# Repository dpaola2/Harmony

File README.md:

# Offline MP3 Player (Harmony2)

Hardware-agnostic MP3 player core with a PC simulator and ESP32 targets. See `docs/README.md` for the doc map; hardware bring-up for Prototype 1 is in `hardware/prototype1/README.md`.

## Current Mark-6 build

The active player uses native ESP-IDF firmware on the Adafruit ESP32 Feather V2. The Python/MicroPython architecture below is retained historical context.

- [Feather bench firmware and instructions](firmware/mark-6/feather-player-bench/README.md)
- [Native UI and renderer](firmware/mark-6/feather-carrier/main/)
- [UI requirements and completion status](docs/Harmony-player-ui-requirements.md)
- [Desktop UI prototype](platforms/pc/ui/README.md)
- [Preserved Mark-7 visual reference](docs/mark-7-design-reference.md)
- [Changelog](CHANGELOG.md)

## Architecture & Goals
- Core app logic in Python, shared by PC simulator and MicroPython on ESP32.
- iPod-style UI: Library → Now Playing → Settings with tactile buttons (no touch).
- Portable storage (SD) and Bluetooth audio on hardware targets; PC sim for fast iteration.
- More context: `PROJECT_OVERVIEW.md` (goals/constraints) and `PLAN.md` (roadmap).

## Development
- **Environment (macOS)**:
  - Install Homebrew if missing: `/bin/bash -c "$(curl -fsSL https://raw.githubusercontent.com/Homebrew/install/HEAD/install.sh)"`.
  - Python: `brew install python` (or `pyenv` if you prefer pinned versions).
  - Recommended tooling: `pipx install uv` (or `pip install uv` in a venv); `pipx ensurepath`.
  - Create venv: `python -m venv .venv && source .venv/bin/activate`.
  - Install dev deps: `python -m pip install --upgrade pip uv pytest`.

- **Run PC simulator** (console UI):
  ```bash
  source .venv/bin/activate
  python -m platforms.pc.main_pc [--music-dir /path/to/Artist/Album/Track.ext]
  ```
  Controls: `w/s` up/down, `a` left, `d` right, `space`/Enter select, `p` play/pause, `b` or `q` back, `x` quit, `+`/`=` volume up, `-` volume down. Defaults to an in-memory demo library.

- **Tests**:
  ```bash
  source .venv/bin/activate
  pytest
  ```
  (Targets `core/` behavior.)

- **ESP32 Prototype 1 upload (demo UI, no buttons required)**:
  - See `hardware/prototype1/README.md` for wiring and flashing details.
  - Convenience script from repo root:
    ```bash
    scripts/upload_proto1_demo.sh /dev/tty.usbmodem*   # adjust port as needed
    ```
    It copies `core/`, `platforms/esp32/*.py`, and `main_esp32.py` to the board and keeps `main.py` as entrypoint.

## Repo structure
- `core/` hardware-agnostic logic and models
- `platforms/pc/` PC simulator (console screen, keyboard input, audio backend)
- `platforms/esp32/` ESP32 adapters (screen, buttons, audio)
- `hardware/` wiring/board notes (prototype phases)
- `enclosure/` mechanical notes
- `tests/` pytest cases for `core/`

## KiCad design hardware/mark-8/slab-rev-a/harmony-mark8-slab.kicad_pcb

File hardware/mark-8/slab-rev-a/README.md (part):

# Harmony Mark-8 "slab" board, revision A

This is the main board of the Mark-8 slab music player, built from `SPEC.md`. It is a 4-layer, 0.8 mm board of 54.4 x 39.6 mm. Every part is on one side and JLCPCB places all of them. When the boards arrive, Dave only flashes them, then adds the screen, the battery and the printed case. No soldering is needed, except for the optional vibration motor (two joints).

**Status: ready to order, with accepted exceptions.** The fixes of the 2026-11-21 pre-order review and of the change review that checked them are in (see "Review dispositions, November 21", its "Change review" table and "Decisions"). ERC 0 errors, 0 warnings; DRC 0 errors, 0 unconnected, 32 silkscreen warnings; `verify.py` passes. The board comes from step C of the touch-wheel re-route: it keeps the checked routing from before the touch review, with the review's layout fixes applied on top by `review_fixes.py`. Eight slow switching nets keep their L3 track behind the touch electrodes, and the two main VBUS paths keep a 0.2 mm bottleneck. Both are accepted exceptions with caps in `design.py`, and the firmware must follow "Firmware for the touch wheel" (see "Touch-wheel re-route"). JLC receives the board in its own frame with rails (`jlcpcb/ORDER.md`). Nothing has been uploaded or ordered.

## What is on the board

```
USB-C J1 ──ESD U8──┬─ D+/D- ── CH9102F U2 ── TXD/RXD (1k) ── ESP32 U1 (UART0)
                   │                   └─ DTR/RTS ── UMH3N Q1 ── EN / IO0
                   ├─ VBUS ── B5819W D1 ───────────────┐
                   ├─ VBUS ── MCP73831 U3 ── VBAT ──────┤
                   └─ CC1/CC2 5.1k to GND              │
JST PH J4 ── AO3401A Q2 (reverse battery) ── VBAT ── AO3401A Q3 (off while VBUS) ── VSYS
                                               │                                    │
                                     MAX17048 U5 (I2C 0x36)      RT9080 U4 ── 3V3 ──┼── ESP32 U1, MPR121 U6, MAX17048 U5 logic
                                                                                    │      └─ AO3401A Q4 ── 3V3_PERIPH ── screen J2, microSD J3
                                                    VSYS ── 10R ── screen LEDA; LEDK ── AO3400A Q5 ── GND (IO4 PWM)
                                                    VSYS ── 33R ── buzzer BZ1 ── AO3400A Q6 (IO2)
                                                    VSYS ── DRV2605L U7 (I2C 0x5A) ── motor pads M+ M-
ESP32 HSPI (14/27/26/33/32, TE 39) ── FH35C J2 (screen)      ESP32 VSPI (5/19/21/25, CD 15) ── DM3AT J3 (microSD)
ESP32 I2C (22/20) ── U5 0x36, U6 0x5B, U7 0x5A               MPR121 U6 ── 9 electrodes on L4 (E1)
```

| Ref | Part | LCSC |
| --- | --- | --- |
| U1 | ESP32-PICO-MINI-02-N8R2 | C2980306 |
| U2 | CH9102F USB to serial | C2858418 |
| U3 | MCP73831T-2ACI/OT charger, PROG 2.7k (about 370 mA) | C424093 |
| U4 | RT9080-33GJ5 3.3 V regulator | C841192 |
| U5 | MAX17048G+T10 fuel gauge | C2682616 |
| U6 | MPR121QR2 touch controller | C91322 |
| U7 | DRV2605LDGSR haptic driver | C527464 |
| U8 | USBLC6-2SC6 USB ESD | C7519 |
| J1 | HRO TYPE-C-31-M-12 USB-C | C165948 |
| J2 | Hirose FH35C-15S-0.3SHW(50) screen FPC | C2889267 |
| J3 | Hirose DM3AT-SF-PEJM5 microSD | C114218 |
| J4 | XYECONN XY-S2B-PH-SM4-TB (JST PH 2.0 side entry) | C54582899 |
| SW1 | Alps SKRTLAE010 side button | C110293 |
| SW2, SW3 | TS-1088-AR02016 BOOT, RESET | C720477 |
| BZ1 | MLT-5020 magnetic buzzer | C94598 |
| Q1 | UMH3N auto-reset | C62892 |
| Q2, Q3, Q4 | AO3401A | C15127 |
| Q5, Q6 | AO3400A | C20917 |
| D1, D2 | B5819W SL | C8598 |
| LED1 | KT-0603R red | C2286 |

The full BOM (40 lines) is `jlcpcb/bom.csv`; the netlist is `netlist.xml`; the schematic is `harmony-mark8-slab.kicad_sch` and `review/schematic.pdf`.

## ESP32 pin map

| GPIO | Module pin | Net | Connects to |
| --- | --- | --- | --- |
| EN | 8 | ESP_EN | 10k to 3V3 (R5), 1 uF (C4), RESET SW3, Q1 |
| 0 | 23 | BOOT | 10k to 3V3 (R6), BOOT SW2, Q1 |
| 1 TXD0 | 31 | U0TXD | 1k R3 to U2 RXD; test pad TP5 |
| 3 RXD0 | 30 | U0RXD | 1k R4 from U2 TXD; test pad TP6 |
| 14 | 18 | LCD_SCK | J2 pin 5 SCLK |
| 27 | 17 | LCD_MOSI | J2 pin 4 SDA |
| 26 | 16 | LCD_CS | J2 pin 7 |
| 33 | 13 | LCD_DC | J2 pin 6 RS |
| 32 | 12 | LCD_RST | J2 pin 8 |
| 4 | 24 | LCD_BL | 100R R15 to Q5 gate, 100k R16 pull-down |
| 39 | 7 | LCD_TE | J2 pin 3 FMARK |
| 5 | 29 | SD_SCK | J3 pin 5 CLK |
| 19 | 33 | SD_MOSI | J3 pin 3 CMD |
| 21 | 35 | SD_MISO | J3 pin 7 DAT0, 10k R21 to 3V3_PERIPH |
| 25 | 15 | SD_CS | J3 pin 2 DAT3, 10k R22 to 3V3_PERIPH |
| 15 | 21 | SD_CD | J3 card-detect switch to GND, 1M R25 to 3V3 |
| 22 | 34 | I2C_SDA | 4.7k R31; U5, U6, U7; test pad TP9 |
| 20 | 26 | I2C_SCL | 4.7k R32; U5, U6, U7; test pad TP10 |
| 34 | 9 | TOUCH_IRQ | U6 IRQ, 10k R11 |
| 38 | 6 | SIDE_BTN | SW1 to GND, 100k R26, 100 nF C23 |
| 13 | 20 | PERIPH_EN_N | 1k R14 to PERIPH_DIV (2.2k R13 to 3V3), 4.7k R34 on to the Q4 gate (1 uF C18 gate to source, 100 nF C26 gate to drain) |
| 2 | 22 | BUZZER | 100R R19 to Q6 gate, 100k R20 pull-down |
| 35 | 10 | VBAT_SENSE | VBAT through 1M R27 / 1M R28, 100 nF C24 |
| 36 | 4 | VBUS_SENSE | VBUS through 100k R29 / 75k R30 (VBUS = pin x 175 / 75) |
| 7, 8 | 27, 28 | GPIO7, GPIO8 | test pads TP7, TP8 |
| 12, 37 | 19, 5 | not connected | IO12 is the MTDI strap |

SD DAT1 and DAT2 have 10k pull-ups (R23, R24) to 3V3_PERIPH. J4: pin 2 is battery +, pin 1 is battery -, marked + and - on the silkscreen.

## Power

- USB VBUS feeds the charger U3, the CH9102F U2 (VDD5 and its VBUS sense) and, through D1, VSYS. C1 10 uF at J1, C7 4.7 uF at U3, C25 100 nF at U2.
- The battery connects through Q2 (P-MOSFET, drain on the J4 + pin, source on VBAT, gate on GND) to VBAT, which has C8 10 uF. Q3 (drain VBAT, source VSYS, gate on VBUS with R9 10k to GND) connects VBAT to VSYS while VBUS is absent. R9 is 10k (it was 100k) so that VBUS bleeds down in tens of milliseconds after an unplug: until it does, VSYS runs on Q3's body diode and 3V3 can sag (review PWR-5). It costs 0.5 mA while USB is plugged in.
- Q2 blocks a reversed pack only while USB is unplugged. With USB plugged in, the charger's preconditioning current turns Q2 on and slowly discharges a reversed pack (about 37 mA) while the charge LED shows charging (review PWR-2). Check the pack polarity with a meter before you connect it.
- VSYS (C9 22 uF) feeds U4 (RT9080, EN on VSYS, C10 1 uF in, C11 4.7 uF out), the 10 R backlight resistor R17, the 33 R buzzer resistor R18 and U7. C11 is a 4.7 uF 10 V X5R 0402 (about 2 uF at 3.3 V; the RT9080 needs more than 1 uF effective at the pin, review PWR-7). The 22 uF C5 at U1 sits behind about 0.22 ohm of track.
- 3V3 feeds U1 (C5 22 uF + C6 100 nF at pin 3), U5 logic side through the I2C pull-ups, U6, the I2C and button pull-ups, U2 VIO and Q4.
- Q4 switches 3V3 to 3V3_PERIPH (screen VCC and IOVCC, microSD VDD, the SD pull-ups). GPIO13 low turns it on, GPIO13 high turns it off. The gate network (review PWR-1, ESP32-2, FW-HW-1; `q4_gate_sim.py`, results in `review/q4-gate-sim.json`):
  - R13 2.2k (3V3 to PERIPH_DIV) and R14 1k (GPIO13 to PERIPH_DIV) form a divider. Driven low, it puts about 1 V on the gate (VGS -2.2 V, Q4 fully on; it draws 1 mA from 3V3 while the rail is on). While EN is low GPIO13 floats and R13 holds the gate at 3V3. After reset release GPIO13 has only its internal pull-down (45k typical, no limits given; simulated 30k to 80k), and the divider holds VGS at -0.09 to -0.22 V, below the AO3401A's -0.5 V minimum threshold: Q4 stays off from reset release until firmware drives GPIO13 low, also in download mode. Leakage at -0.22 V is about 0.2 uA (2.4 uA for a hot part at the threshold minimum).
  - Off means that Q4 does not conduct. It does not mean that 3V3_PERIPH is at 0 V. Until firmware runs, and all the time in download mode, the ESP32's reset pull-ups on GPIO5 (SD_SCK) and GPIO14 (LCD_SCK) feed the unpowered card and screen through their input clamps, so 3V3_PERIPH can sit at about 1 to 2.5 V (change review, Q4 missed item). The current is tens of microamps and harms nothing. To check Q4 at bring-up, hold the board in download mode and measure 3V3 minus PERIPH_GATE: it must be 0.25 V or less. 3V3_PERIPH under 0.1 V is a valid check only with the screen and the card removed.
  - R34 4.7k (PERIPH_DIV to PERIPH_GATE) and C26 100 nF (gate to drain) set the turn-on ramp: on the Miller plateau the gate current through R34 flows through C26, so the drain rises at a controlled rate. C18 1 uF (gate to source) keeps the gate on 3V3 while 3V3 itself powers up: VGS stays above about -0.37 V (with C18 15 percent low and C26 10 percent high), and the rail stays below 0.04 V.
  - Simulated across VGS(th) -0.5 to -1.3 V, K 5 to 18 A/V2, 10 to 30 uF and 0 to 100 mA on 3V3_PERIPH, the RT9080 at its 610 mA minimum current limit, C11 at 1.3 uF (the low end for the 4.7 uF 0402 at 3.3 V) and 250 mA for the ESP32: 3V3_PERIPH reaches 90 percent 3.3 to 10.1 ms after GPIO13 goes low (10 to 90 percent in 1.0 to 3.2 ms), Q4 peaks at 161 mA (100 mA of it the resistive load), and 3V3 at U1 stays at 3.22 V or more. The 3.22 V figure assumes the RT9080's nominal 3.30 V and a full battery. With the set point 2 percent low it is about 3.16 V, and with a low battery (VSYS 3.45 V, the RT9080 in dropout) about 3.03 to 3.09 V. The turn-on itself costs 10 mV or less (55 mV or less in dropout). The old network (100k, 10k, 100 nF) gave 0.36 to 1.0 ms, up to 0.96 A and 3V3 down to 1.74 V in the same model. Q4 stops conducting 3.5 to 10.6 ms after GPIO13 goes high at 25 C (up to about 21 ms for a hot part); the rail then drains slowly through its loads. After a reset, Q4 turns off up to about 20 ms after reset release (change review Q4-4).
  - C19 10 uF + C20 100 nF at J2, C21 10 uF + C22 100 nF at J3.
- U2 CH9102F: VDD5 and VBUS from USB VBUS, V3 decoupled by C2, VIO on 3V3 with C3. This is WCH's dual-supply scheme: on battery VDD5 is at 0 V, VIO draws about 2 uA and the chip does not back-feed (CH9102 datasheet 5.2).
- Deep-sleep estimate with Q4 off, U2 unpowered, U6 in stop mode, U7 in standby: ESP32-PICO-MINI-02 about 10 uA, U5 3 to 23 uA (hibernate or active), U6 about 3 uA, U7 about 4 uA, U4 2 uA, VBAT divider 2.1 uA, U3 reverse current under 2 uA, D1 reverse leakage 6 to 15 uA (review PWR-11): about 36 to 65 uA. With touch wake on (the player default), U6 runs a slow scan instead of stop mode: about 11 uA instead of 3. With a card in J3, the card-detect switch also draws 3.3 uA through R25 (3.3 V / 1M; it was 33 uA with 100k). All are under the 100 uA target.

Firmware notes that follow from the hardware:
1. Drive every screen and card line low, or make it an input, before setting GPIO13 high (Q4 off), or the ESP32 back-powers the screen and card through their input protection (SPEC 5.3).
2. Touch wake needs the MPR121 running (a slow scan), not stop mode. The 100 uA budget above assumes stop mode; measure the run-mode current before relying on touch wake.
3. The backlight runs from VSYS through 10 R: about 120 mA at 4.2 V battery and about 170 mA on USB (VSYS 4.7 V) at 100 percent duty, up to about 220 mA with a low-VF panel on a 5.25 V port (review PERIPH-2). R17 is a 1206 rated 0.25 W; keep the duty cycle at or below 80 percent on USB, and compute the R17 power cap from a worst-case model (VF 2.7 V, 10 ohm), not the brightness model.
4. GPIO15 (SD_CD) is the MTDO strap: a card in the slot silences the ROM boot log. GPIO2 (BUZZER) has R20 100k to GND, so the strap stays low at boot. R25 is 1M, so read SD_CD twice a few milliseconds apart before acting on a change.
5. The microSD lines are long and cross the touch wheel on L1 behind the L2 hatch (they do not go around it): SD_MOSI 88 mm, SD_SCK 82 mm (35 mm of it over the hatch), SD_MISO 77 mm, SD_CS 33 mm; the screen lines are 17 to 45 mm. SD_SCK has no series resistor: set the card's GPIOs to drive strength 0 or 1 before mounting (review L6). Start the card at 20 MHz SPI and drop to 10 MHz if reads fail.
6. Wait at least 20 ms after driving GPIO13 low before driving any screen or card line high (`SLAB_PERIPH_RAMP_MS`, see "Power"). After driving GPIO13 high, the rail needs about 0.4 s to drain below 0.5 V through its loads, so a real card power cycle needs that wait (review CC-2).
7. VBUS_SENSE is VBUS x 75 / 175: 5.0 V gives 2.14 V and 5.25 V gives 2.25 V at GPIO36, inside the ADC's calibrated range up to 5.7 V. `SLAB_VBUS_DIVIDER_X1000` is 2333; the 4300 mV present threshold is 1.84 V at the pin. GPIO36 has no filter capacitor (Espressif asks for 0.1 uF; the source is 43 kOhm), so average several ADC samples for each VBUS reading (change review Q4-5). Revision B adds 100 nF from GPIO36 to GND.

## Layout

The board sits behind the wheel, touch side (L4) against the front skin, component side toward the back plate. KiCad shows the component side, so left and right are swapped against the device front view. Every position in this README and in `mechanical-interface.json` is in device coordinates (SPEC 1); `design.py` holds the transform (`to_kicad`, `to_device`).

| Area (device) | What is there |
| --- | --- |
| Top left | J4 battery connector (cable to +Y), Q2, charger U3, Q3, D1, regulator U4, fuel gauge U5, bulk caps |
| Left edge, lower | haptic driver U7 and motor pads M+ M- |
| Behind the left part of the wheel (FPC leg zone) | Q4 and its gate network (R13, R14, R34, C18, C26) |
| Right edge | U1 with its antenna end flush with x = +27.2; SW1 side button above it, actuator through the right wall |
| Top right | BOOT SW2, RESET SW3, side-button RC, I2C pull-up R31 in the top strip; R32 just below the top buses, behind the wheel. Nothing in the antenna's open-end clearance below SW1 |
| Behind the wheel centre | MPR121 U6 with its parts, buzzer BZ1 and its driver, the J2 decoupling |
| Right of centre, just above the ramp zone | backlight switch Q5 (its body ends 0.05 above the ramp zone); its gate resistors R15 and R16 sit in the ramp zone (0402, 0.35 tall, under the 0.6 limit) |
| Bottom centre | USB-C J1 (mating face y = -50.4), screen connector J2 just above it (slot toward +X, into the empty ramp) |
| Bottom left | microSD J3 (card enters from -Y), its pull-ups in one row above the contacts, charge LED1 between J3 and J1 |
| Bottom right | ESD U8, CH9102F U2, auto-reset Q1, CC resistors, VBUS and VBAT sense dividers, EN RC |

### Touch wheel

- L4 carries nine copper zones: a centre disc r <= 7.0 and eight ring sectors from r 7.8 to 16.6, each boundary a three-tooth sawtooth (0.9 mm tangential half-amplitude) offset 0.2 each side, so neighbours are exactly 0.4 apart (checked by `verify.py`). ELE1 is at 12 o'clock seen from the front, then clockwise (`wheel.py`). Each electrode connects through one plated pad of E1 to an MPR121 pin, by an L1 track where one fits and otherwise partly on L3.
- L2 under the wheel is a 25 percent GND hatch (0.2 mm lines, 1.3 mm gaps, 45 degrees) out to r 17.6. The L4 GND pour and the L1 GND pour stop at r 17.6.
- L3 lies about 0.1 mm behind the L4 electrodes, with no ground between them. A track there couples into the electrode above it (about 0.5 pF per 10 mm of 0.15 mm track), and one edge during an MPR121 charge window can shift a reading by about as much as a touch (NXP AN3863: keep other signals on the far side of the ground layer). So inside the electrode disc plus 0.5 mm (r <= 17.1, `WHEEL_KEEPOUT_R`) only DC and static nets and the electrode lines may run on L3 or place vias: 3V3, 3V3_PERIPH, VBUS, VSYS, VBAT, BAT_P, LCD_RST, PERIPH_EN_N, PERIPH_DIV, PERIPH_GATE, SD_CD, SIDE_BTN, TOUCH_IRQ, BOOT, ESP_EN, CHG_STAT, VBAT_SENSE, VBUS_SENSE, GND and ELE0 to ELE8 (`WHEEL_TOLERANT_NETS` in `design.py`). BOOT, ESP_EN, PERIPH_DIV, PERIPH_GATE, CHG_STAT and the two sense dividers are not on the list the touch review gave; they only change at reset, at power switching or on a charge state change, never during a scan. LCD_LEDA is not static: with no capacitor on it, it swings 1.2 to 2.2 V at the backlight PWM rate (review PERIPH-1). Since 2026-11-21 it is an accepted exception like the seven below, not a DC net. VBUS (charger and adapter ripple while plugged in) and 3V3_PERIPH (card current spikes) also carry some AC, so log the touch noise while charging from a cheap adapter and during card read bursts too (review L10).
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
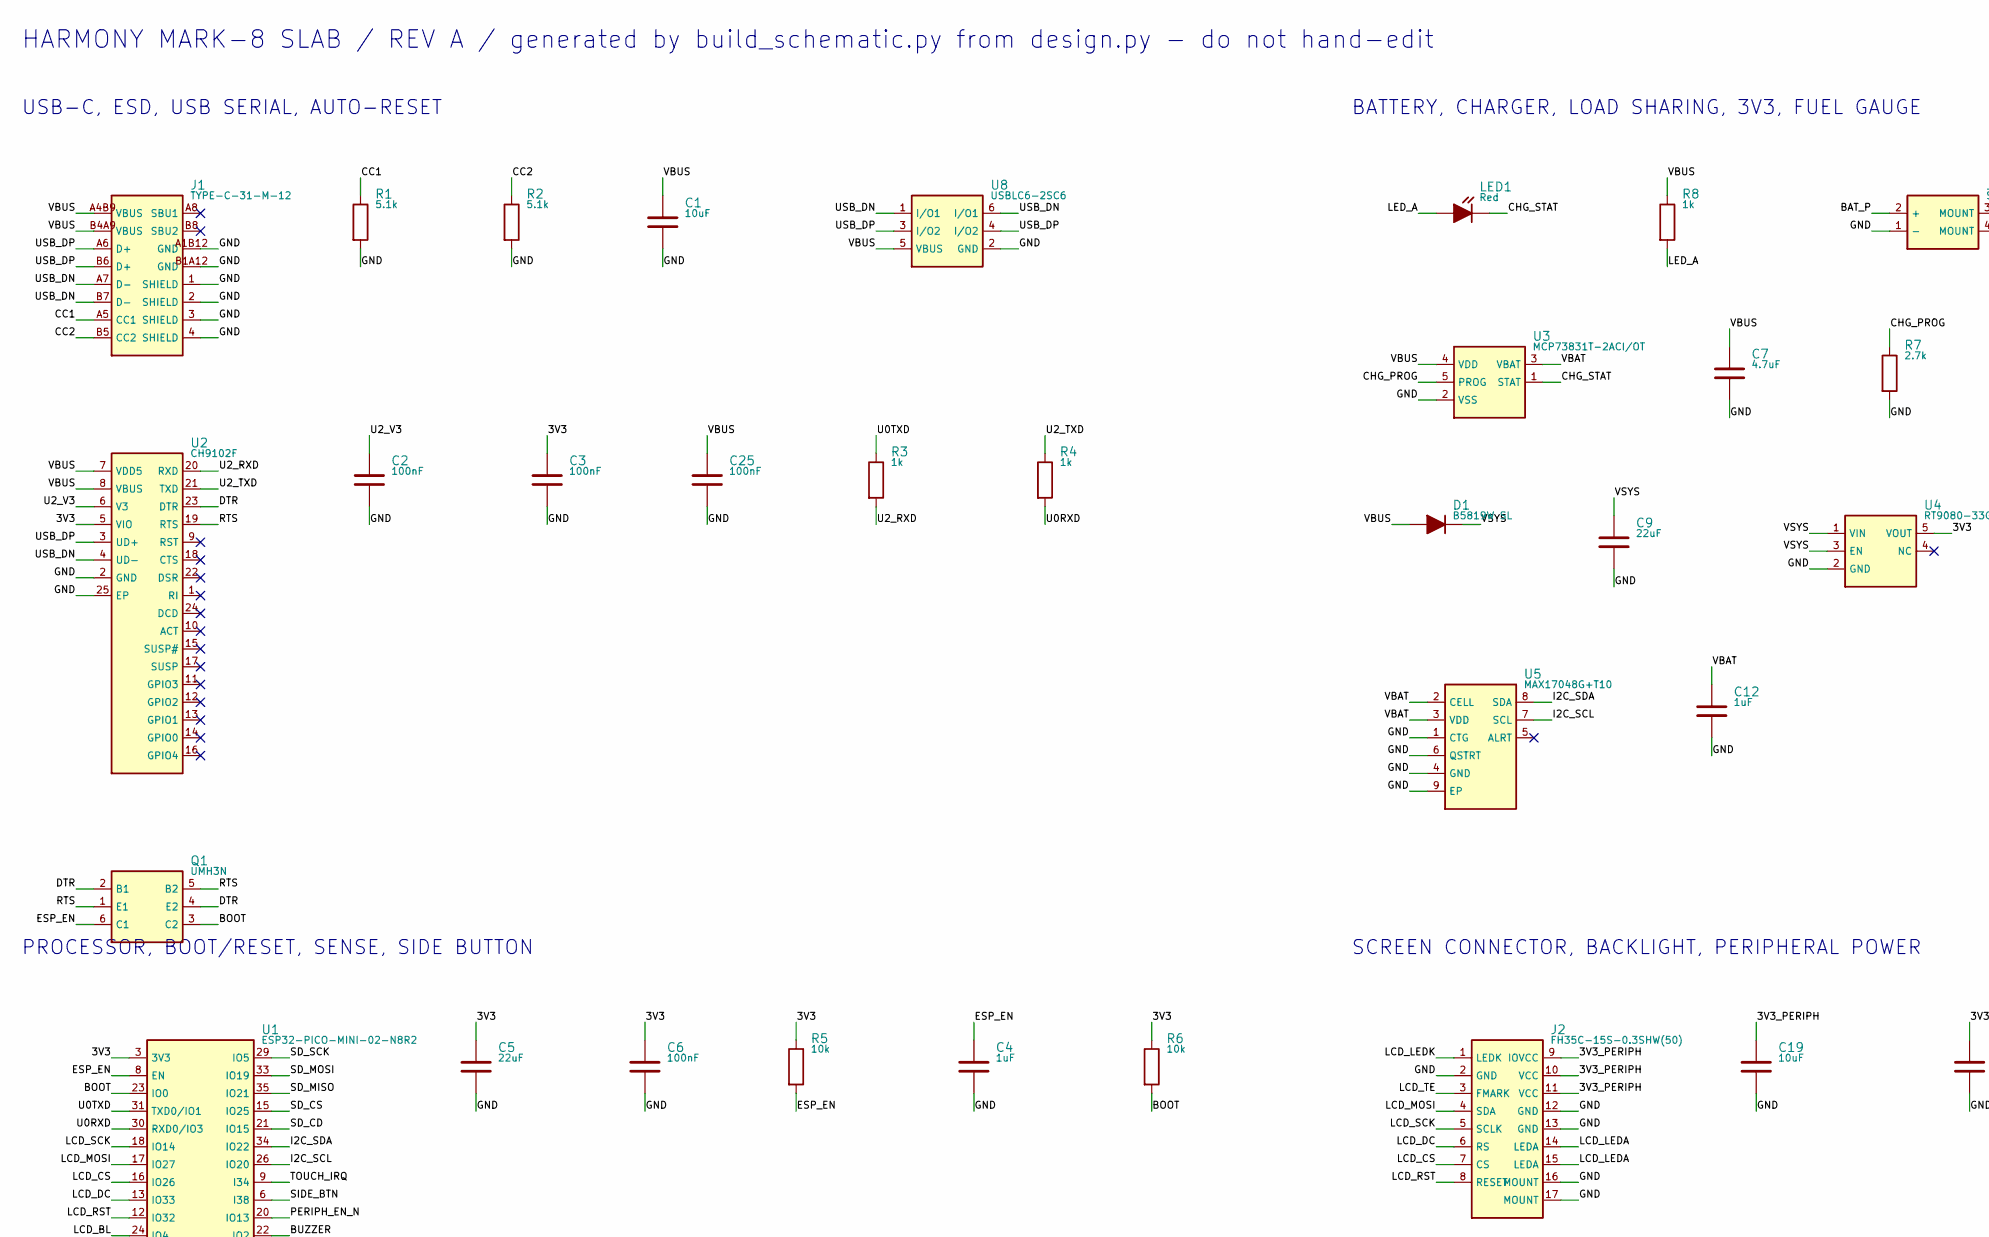
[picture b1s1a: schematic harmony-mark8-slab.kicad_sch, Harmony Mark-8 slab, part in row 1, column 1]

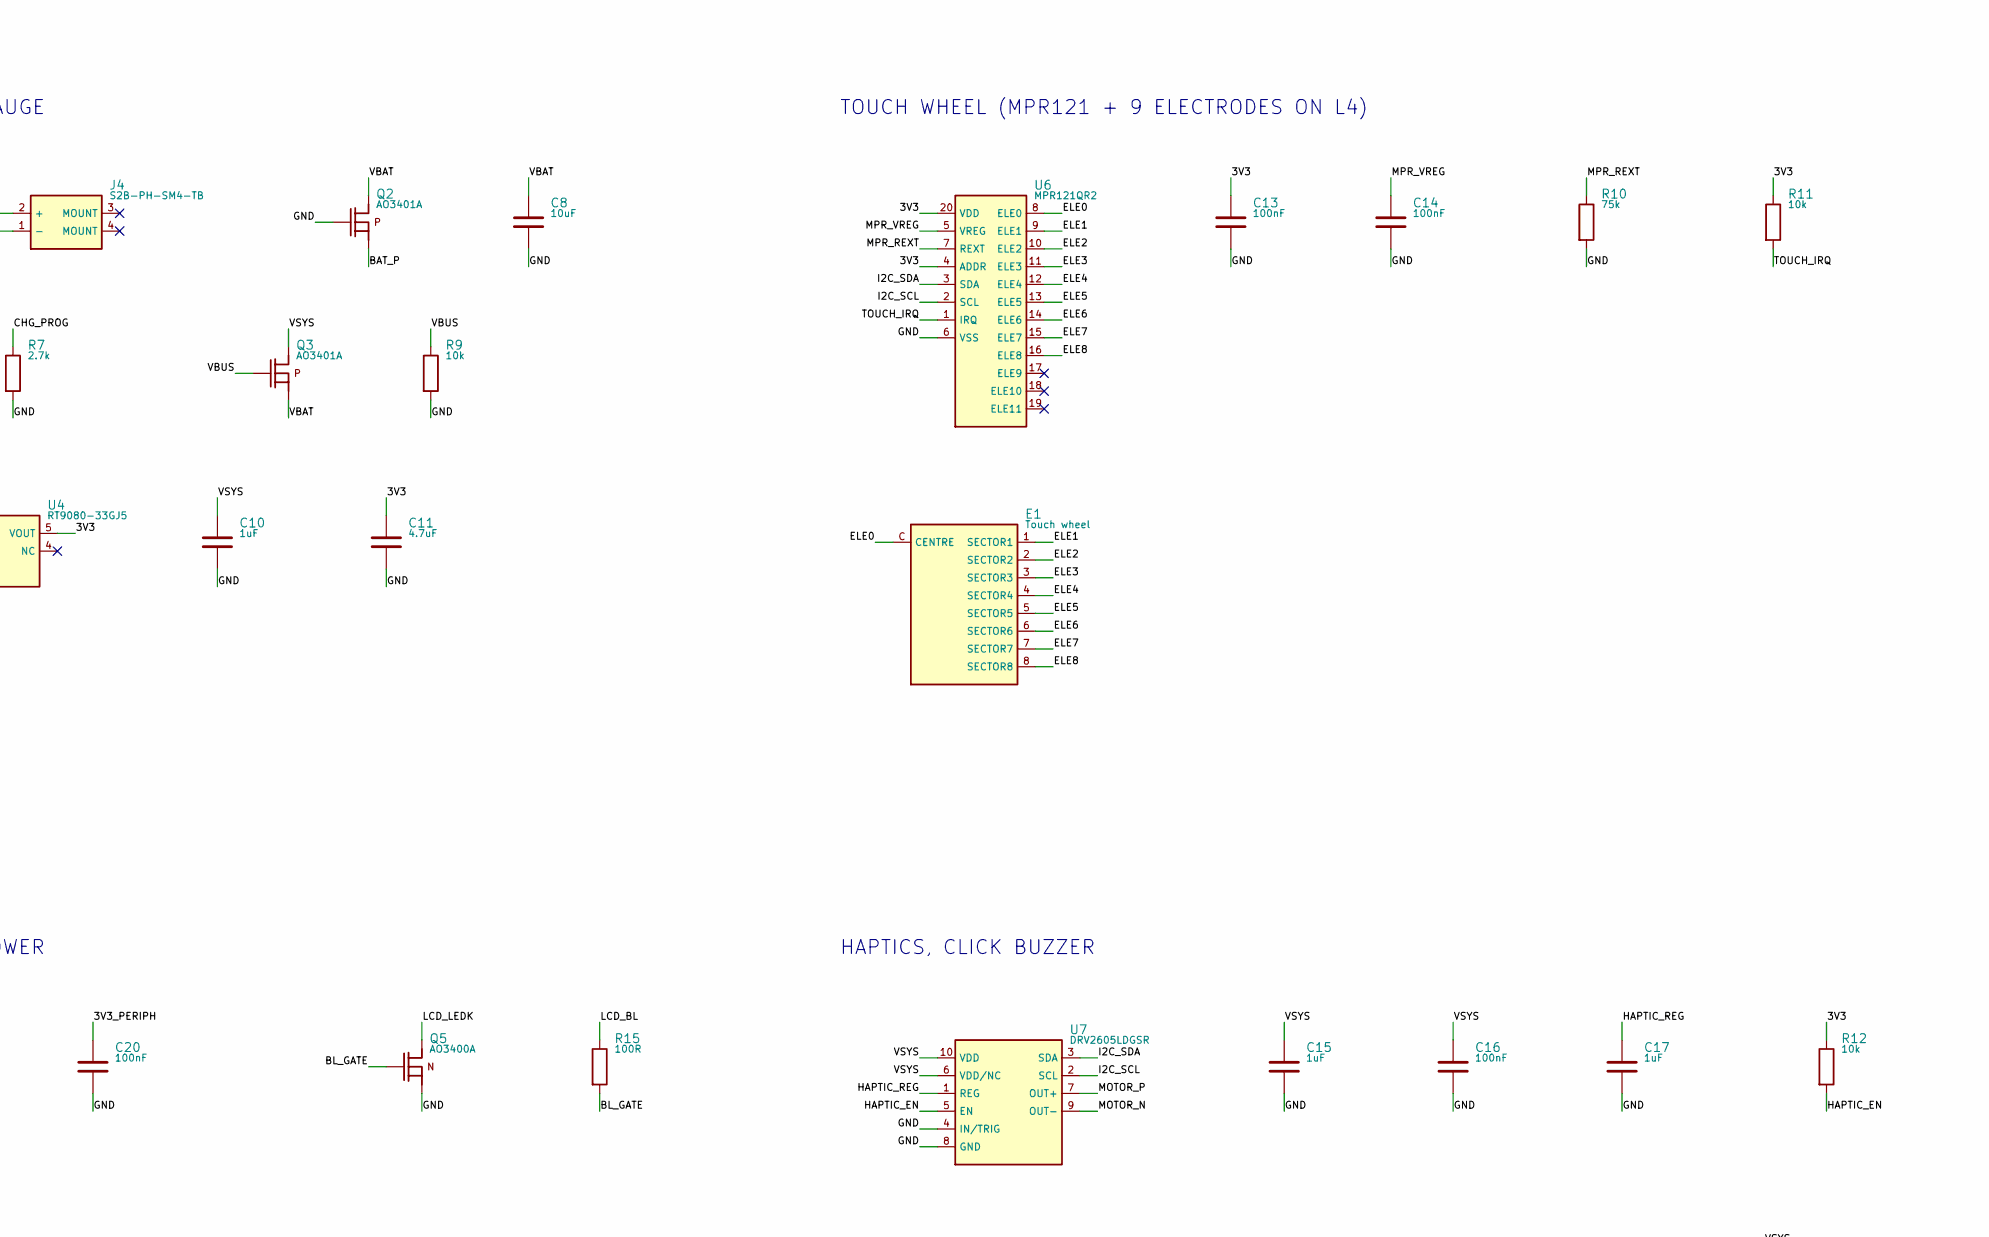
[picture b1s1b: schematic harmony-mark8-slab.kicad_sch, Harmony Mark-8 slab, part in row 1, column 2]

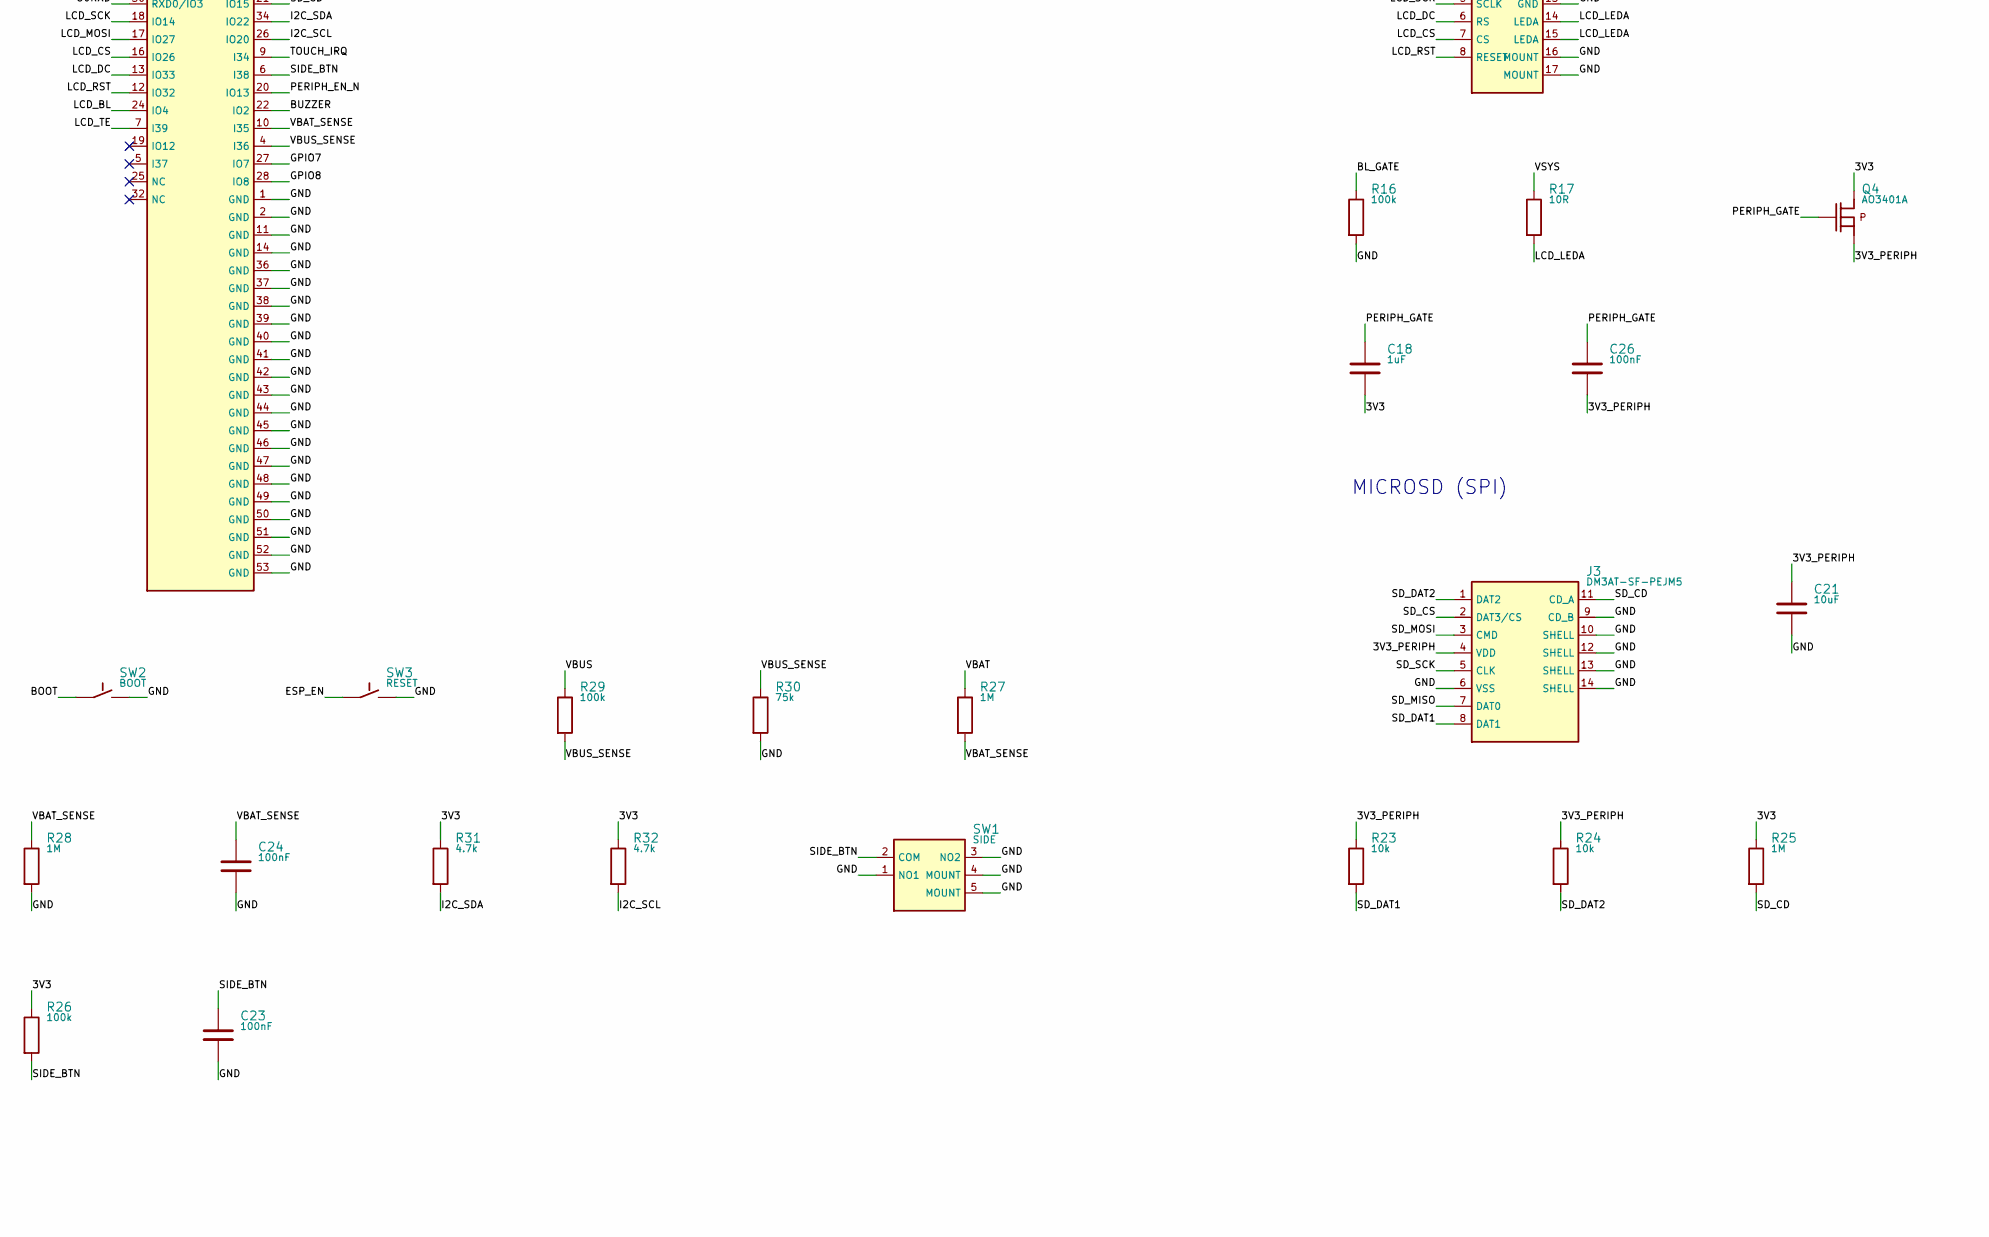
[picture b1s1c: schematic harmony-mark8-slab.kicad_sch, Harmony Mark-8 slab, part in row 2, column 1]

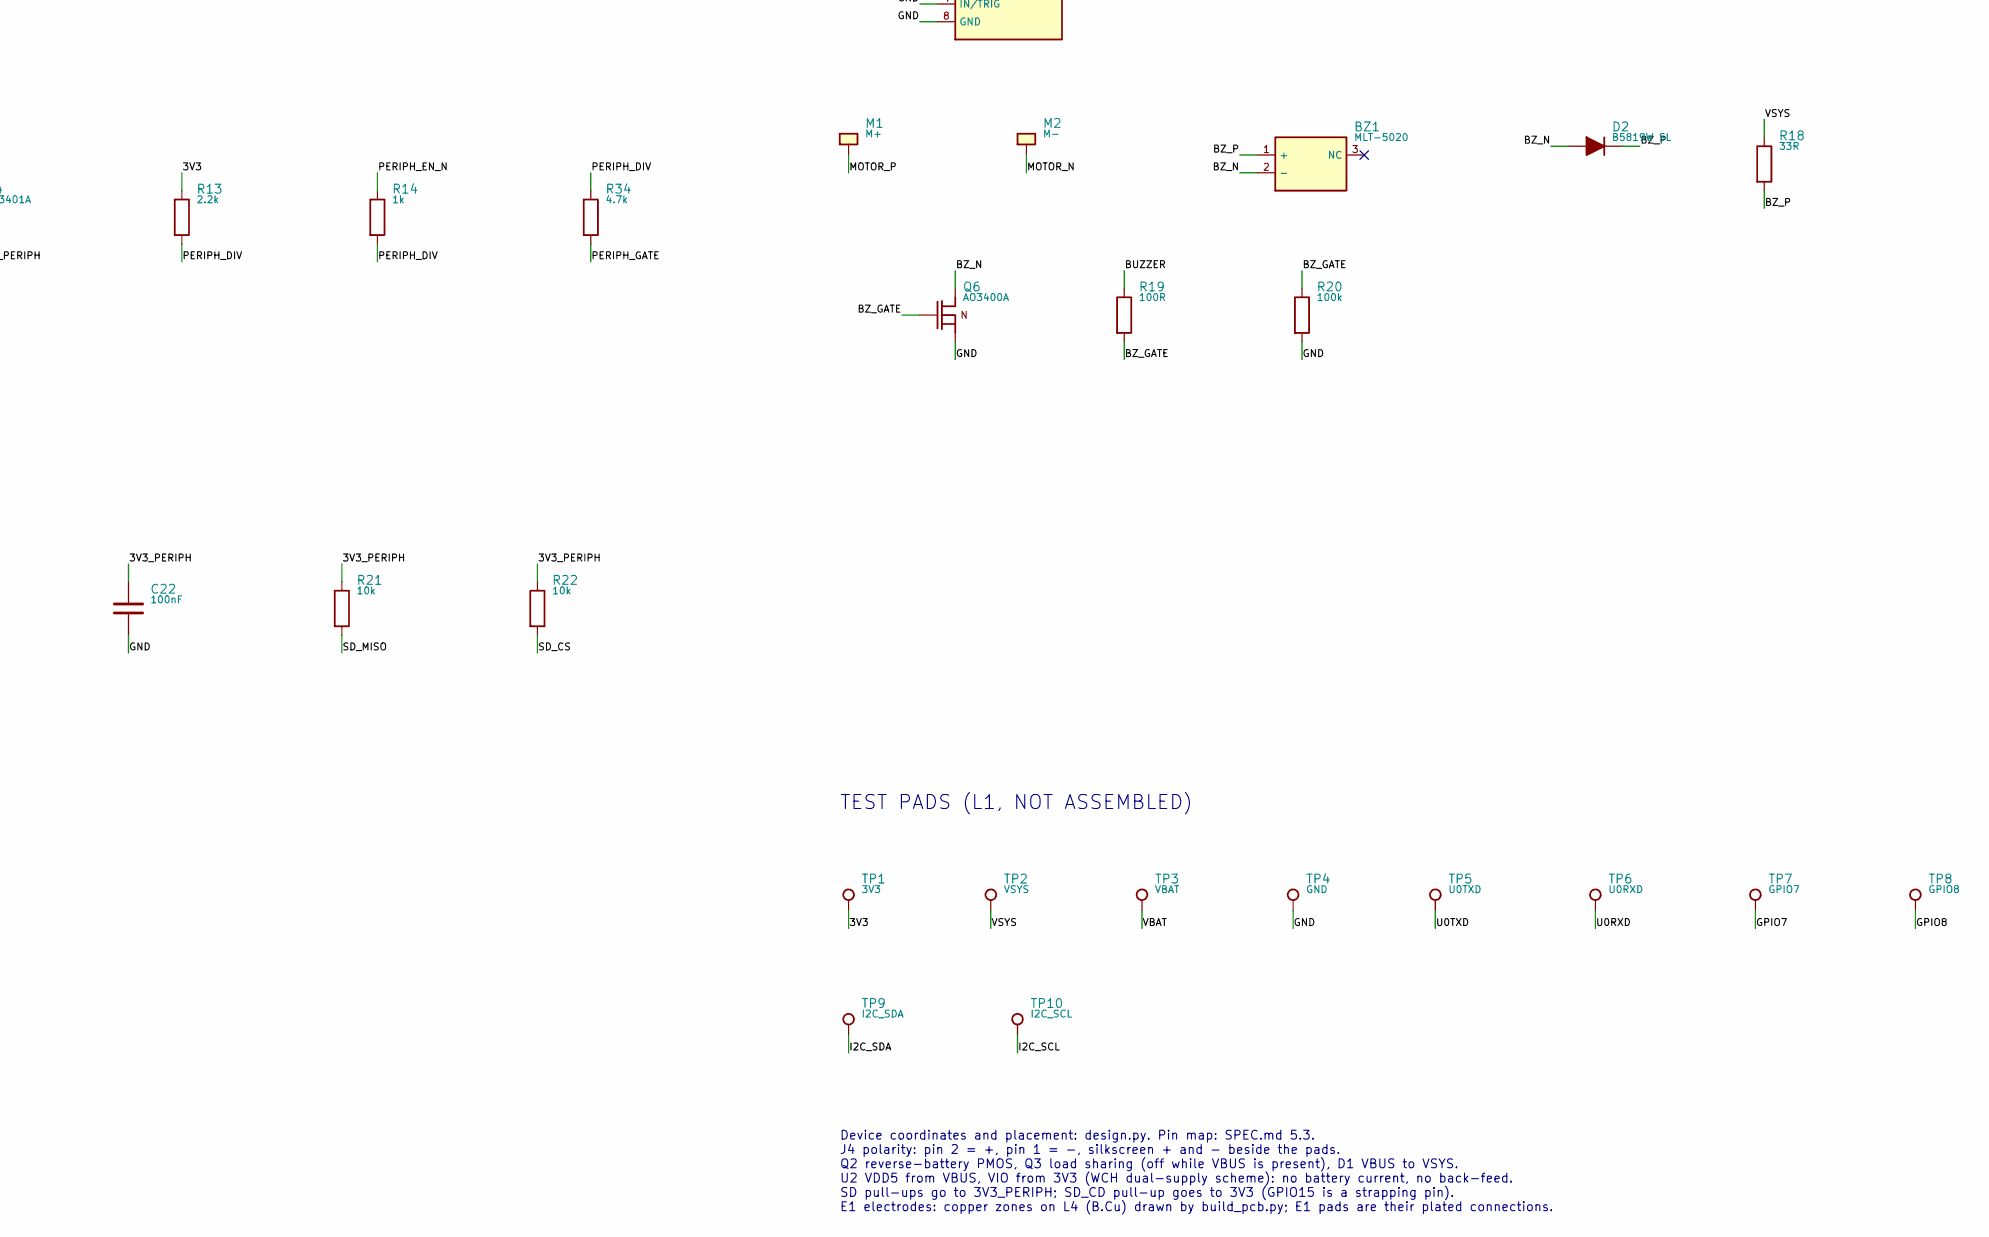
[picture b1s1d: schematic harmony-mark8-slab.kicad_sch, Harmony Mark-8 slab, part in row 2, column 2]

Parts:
BZ1: MLT-5020; Buzzer_MLT-5020; MPN Huawha MLT-5020; LCSC C94598
C1: 10uF; C_0805_2012Metric; LCSC C15850
C2, C3, C6, C13, C14, C16, C20, C22, C23, C24, C25, C26: 100nF; C_0402_1005Metric; LCSC C1525
C4, C10, C12, C15, C17, C18: 1uF; C_0402_1005Metric; LCSC C52923
C5: 22uF; C_0603_1608Metric; LCSC C59461
C7: 4.7uF; C_0603_1608Metric; LCSC C19666
C8, C19, C21: 10uF; C_0603_1608Metric; LCSC C19702
C9: 22uF; C_0805_2012Metric; LCSC C45783
C11: 4.7uF; C_0402_1005Metric; LCSC C23733
D1, D2: B5819W SL; SOD-123_B5819W; MPN CJ B5819W SL; LCSC C8598
E1: Touch wheel; TouchWheel
J1: TYPE-C-31-M-12; USB-C_HRO_TYPE-C-31-M-12; MPN HRO TYPE-C-31-M-12; LCSC C165948
J2: FH35C-15S-0.3SHW(50); FH35C-15S-0.3SHW; MPN Hirose FH35C-15S-0.3SHW(50); LCSC C2889267
J3: DM3AT-SF-PEJM5; MPN Hirose DM3AT-SF-PEJM5; LCSC C114218
J4: S2B-PH-SM4-TB; JST_PH_S2B-PH-SM4-TB; MPN XYECONN XY-S2B-PH-SM4-TB (JST PH 2.0 si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; LCSC C54582899
LED1: Red; LED_0603_EasyEDA; MPN KENTO KT-0603R; LCSC C2286
M1: M+; MotorPad_2.0x1.5
M2: M-; MotorPad_2.0x1.5
Q1: UMH3N; SOT-363; MPN UMH3N dual DTC143T; LCSC C62892
Q2, Q3, Q4: AO3401A; SOT-23_AO3401A; MPN AOS AO3401A; LCSC C15127
Q5, Q6: AO3400A; SOT-23_AO3400A; MPN AOS AO3400A; LCSC C20917
R1, R2: 5.1k; R_0402_1005Metric; LCSC C25905
R3, R4, R8, R14: 1k; R_0402_1005Metric; LCSC C11702
R5, R6, R9, R11, R12, R21, R22, R23, R24: 10k; R_0402_1005Metric; LCSC C25744
R7: 2.7k; R_0603_1608Metric; LCSC C13167
R10, R30: 75k; R_0603_1608Metric; LCSC C23242
R13: 2.2k; R_0402_1005Metric; LCSC C25879
R15, R19: 100R; R_0402_1005Metric; LCSC C25076
R16, R20, R26, R29: 100k; R_0402_1005Metric; LCSC C25741
R17: 10R; R_1206_3216Metric; LCSC C17903
R18: 33R; R_0805_2012Metric; LCSC C17634
R25, R27, R28: 1M; R_0402_1005Metric; LCSC C26083
R31, R32, R34: 4.7k; R_0402_1005Metric; LCSC C25900
SW1: SIDE; SW_SKRTLAE010; MPN Alps SKRTLAE010; LCSC C110293
SW2: BOOT; SW_TS-1088; MPN XKB TS-1088-AR02016; LCSC C720477
SW3: RESET; SW_TS-1088; MPN XKB TS-1088-AR02016; LCSC C720477
TP1: 3V3; TestPoint_Pad_D1.0mm
TP2: VSYS; TestPoint_Pad_D1.0mm
TP3: VBAT; TestPoint_Pad_D1.0mm
TP4: GND; TestPoint_Pad_D1.0mm
TP5: U0TXD; TestPoint_Pad_D1.0mm
TP6: U0RXD; TestPoint_Pad_D1.0mm
TP7: GPIO7; TestPoint_Pad_D1.0mm
TP8: GPIO8; TestPoint_Pad_D1.0mm
TP9: I2C_SDA; TestPoint_Pad_D1.0mm
TP10: I2C_SCL; TestPoint_Pad_D1.0mm
U1: ESP32-PICO-MINI-02-N8R2; ESP32-PICO-MINI-02; MPN Espressif ESP32-PICO-MINI-02-N8R2; LCSC C2980306
U2: CH9102F; QFN-24_4x4_P0.5_EP2.5; MPN WCH CH9102F; LCSC C2858418
U3: MCP73831T-2ACI/OT; SOT-23-5_MCP73831; MPN Microchip MCP73831T-2ACI/OT; LCSC C424093
U4: RT9080-33GJ5; TSOT-23-5_RT9080; MPN Richtek RT9080-33GJ5; LCSC C841192
U5: MAX17048G+T10; TDFN-8_2x2_P0.5_EP; MPN Analog MAX17048G+T10; LCSC C2682616
U6: MPR121QR2; QFN-20_3x3_P0.4; MPN NXP MPR121QR2; LCSC C91322
U7: DRV2605LDGSR; VSSOP-10_DRV2605L; MPN TI DRV2605LDGSR; LCSC C527464
U8: USBLC6-2SC6; SOT-23-6; MPN STMicro USBLC6-2SC6; LCSC C7519

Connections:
3V3: C3.1, C5.1, C6.1, C11.1, C13.1, C18.2, Q4.2 (S), R5.1, R6.1, R11.1, R12.1, R13.1, R25.1, R26.1, R31.1, R32.1, TP1.1, U1.3 (3V3), U2.5 (VIO), U4.5 (VOUT), U6.4 (ADDR), U6.20 (VDD)
3V3_PERIPH: C19.1, C20.1, C21.1, C22.1, C26.2, J2.9 (IOVCC), J2.10 (VCC), J2.11 (VCC), J3.4 (VDD), Q4.3 (D), R21.1, R22.1, R23.1, R24.1
BAT_P: J4.2 (+), Q2.3 (D)
BL_GATE: Q5.1 (G), R15.2, R16.1
BOOT: Q1.3 (C2), R6.2, SW2.1, U1.23 (IO0)
BUZZER: R19.1, U1.22 (IO2)
BZ_GATE: Q6.1 (G), R19.2, R20.1
BZ_N: BZ1.2 (-), D2.2 (A), Q6.3 (D)
BZ_P: BZ1.1 (+), D2.1 (K), R18.2
CC1: J1.A5 (CC1), R1.1
CC2: J1.B5 (CC2), R2.1
CHG_PROG: R7.1, U3.5 (PROG)
CHG_STAT: LED1.2 (K), U3.1 (STAT)
DTR: Q1.2 (B1), Q1.4 (E2), U2.23 (DTR)
ELE0: E1.C (CENTRE), U6.8 (ELE0)
ELE1: E1.1 (SECTOR1), U6.9 (ELE1)
ELE2: E1.2 (SECTOR2), U6.10 (ELE2)
ELE3: E1.3 (SECTOR3), U6.11 (ELE3)
ELE4: E1.4 (SECTOR4), U6.12 (ELE4)
ELE5: E1.5 (SECTOR5), U6.13 (ELE5)
ELE6: E1.6 (SECTOR6), U6.14 (ELE6)
ELE7: E1.7 (SECTOR7), U6.15 (ELE7)
ELE8: E1.8 (SECTOR8), U6.16 (ELE8)
ESP_EN: C4.1, Q1.6 (C1), R5.2, SW3.1, U1.8 (EN)
GND: C1.2, C2.2, C3.2, C4.2, C5.2, C6.2, C7.2, C8.2, C9.2, C10.2, C11.2, C12.2, C13.2, C14.2, C15.2, C16.2, C17.2, C19.2, C20.2, C21.2, C22.2, C23.2, C24.2, C25.2, J1.1 (SHIELD), J1.2 (SHIELD), J1.3 (SHIELD), J1.4 (SHIELD), J1.A1B12 (GND), J1.B1A12 (GND), J2.2 (GND), J2.12 (GND), J2.13 (GND), J2.16 (MOUNT), J2.17 (MOUNT), J3.6 (VSS), J3.9 (CD_B), J3.10 (SHELL), J3.12 (SHELL), J3.13 (SHELL), J3.14 (SHELL), J4.1 (-), Q2.1 (G), Q5.2 (S), Q6.2 (S), R1.2, R2.2, R7.2, R9.2, R10.2, R16.2, R20.2, R28.2, R30.2, SW1.1 (NO1), SW1.3 (NO2), SW1.4 (MOUNT), SW1.5 (MOUNT), SW2.2, SW3.2, TP4.1, U1.1 (GND), U1.2 (GND), U1.11 (GND), U1.14 (GND), U1.36 (GND), U1.37 (GND), U1.38 (GND), U1.39 (GND), U1.40 (GND), U1.41 (GND), U1.42 (GND), U1.43 (GND), U1.44 (GND), U1.45 (GND), U1.46 (GND), U1.47 (GND), U1.48 (GND), U1.49 (GND), U1.50 (GND), U1.51 (GND), U1.52 (GND), U1.53 (GND), U2.2 (GND), U2.25 (EP), U3.2 (VSS), U4.2 (GND), U5.1 (CTG), U5.4 (GND), U5.6 (QSTRT), U5.9 (EP), U6.6 (VSS), U7.4 (IN/TRIG), U7.8 (GND), U8.2 (GND)
GPIO7: TP7.1, U1.27 (IO7)
GPIO8: TP8.1, U1.28 (IO8)
HAPTIC_EN: R12.2, U7.5 (EN)
HAPTIC_REG: C17.1, U7.1 (REG)
I2C_SCL: R32.2, TP10.1, U1.26 (IO20), U5.7 (SCL), U6.2 (SCL), U7.2 (SCL)
I2C_SDA: R31.2, TP9.1, U1.34 (IO22), U5.8 (SDA), U6.3 (SDA), U7.3 (SDA)
LCD_BL: R15.1, U1.24 (IO4)
LCD_CS: J2.7 (CS), U1.16 (IO26)
LCD_DC: J2.6 (RS), U1.13 (IO33)
LCD_LEDA: J2.14 (LEDA), J2.15 (LEDA), R17.2
LCD_LEDK: J2.1 (LEDK), Q5.3 (D)
LCD_MOSI: J2.4 (SDA), U1.17 (IO27)
LCD_RST: J2.8 (RESET), U1.12 (IO32)
LCD_SCK: J2.5 (SCLK), U1.18 (IO14)
LCD_TE: J2.3 (FMARK), U1.7 (I39)
LED_A: LED1.1 (A), R8.2
MOTOR_N: M2.1, U7.9 (OUT-)
MOTOR_P: M1.1, U7.7 (OUT+)
MPR_REXT: R10.1, U6.7 (REXT)
MPR_VREG: C14.1, U6.5 (VREG)
PERIPH_DIV: R13.2, R14.2, R34.1
PERIPH_EN_N: R14.1, U1.20 (IO13)
PERIPH_GATE: C18.1, C26.1, Q4.1 (G), R34.2
RTS: Q1.1 (E1), Q1.5 (B2), U2.19 (RTS)
SD_CD: J3.11 (CD_A), R25.2, U1.21 (IO15)
SD_CS: J3.2 (DAT3/CS), R22.2, U1.15 (IO25)
SD_DAT1: J3.8 (DAT1), R23.2
SD_DAT2: J3.1 (DAT2), R24.2
SD_MISO: J3.7 (DAT0), R21.2, U1.35 (IO21)
SD_MOSI: J3.3 (CMD), U1.33 (IO19)
SD_SCK: J3.5 (CLK), U1.29 (IO5)
SIDE_BTN: C23.1, R26.2, SW1.2 (COM), U1.6 (I38)
TOUCH_IRQ: R11.2, U1.9 (I34), U6.1 (IRQ)
U0RXD: R4.2, TP6.1, U1.30 (RXD0/IO3)
U0TXD: R3.1, TP5.1, U1.31 (TXD0/IO1)
U2_RXD: R3.2, U2.20 (RXD)
U2_TXD: R4.1, U2.21 (TXD)
U2_V3: C2.1, U2.6 (V3)
USB_DN: J1.A7 (D-), J1.B7 (D-), U2.4 (UD-), U8.1 (I/O1), U8.6 (I/O1)
USB_DP: J1.A6 (D+), J1.B6 (D+), U2.3 (UD+), U8.3 (I/O2), U8.4 (I/O2)
VBAT: C8.1, C12.1, Q2.2 (S), Q3.3 (D), R27.1, TP3.1, U3.3 (VBAT), U5.2 (CELL), U5.3 (VDD)
VBAT_SENSE: C24.1, R27.2, R28.1, U1.10 (I35)
VBUS: C1.1, C7.1, C25.1, D1.2 (A), J1.A4B9 (VBUS), J1.B4A9 (VBUS), Q3.1 (G), R8.1, R9.1, R29.1, U2.7 (VDD5), U2.8 (VBUS), U3.4 (VDD), U8.5 (VBUS)
VBUS_SENSE: R29.2, R30.1, U1.4 (I36)
VSYS: C9.1, C10.1, C15.1, C16.1, D1.1 (K), Q3.2 (S), R17.1, R18.1, TP2.1, U4.1 (VIN), U4.3 (EN), U7.6 (VDD/NC), U7.10 (VDD)

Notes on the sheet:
USB-C, ESD, USB SERIAL, AUTO-RESET
PROCESSOR, BOOT/RESET, SENSE, SIDE BUTTON
BATTERY, CHARGER, LOAD SHARING, 3V3, FUEL GAUGE
SCREEN CONNECTOR, BACKLIGHT, PERIPHERAL POWER
MICROSD (SPI)
TOUCH WHEEL (MPR121 + 9 ELECTRODES ON L4)
HAPTICS, CLICK BUZZER
TEST PADS (L1, NOT ASSEMBLED)
HARMONY MARK-8 SLAB / REV A / generated by build_schematic.py from design.py - do not hand-edit
Device coordinates and placement: design.py. Pin map: SPEC.md 5.3. J4 polarity: pin 2 = +, pin 1 = -, silkscreen + and - beside the pads. Q2 reverse-battery PMOS, Q3 load sharing (off while VBUS is present), D1 VBUS to VSYS. U2 VDD5 from VBUS, VIO from 3V3 (WCH dual-supply scheme): no battery curre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

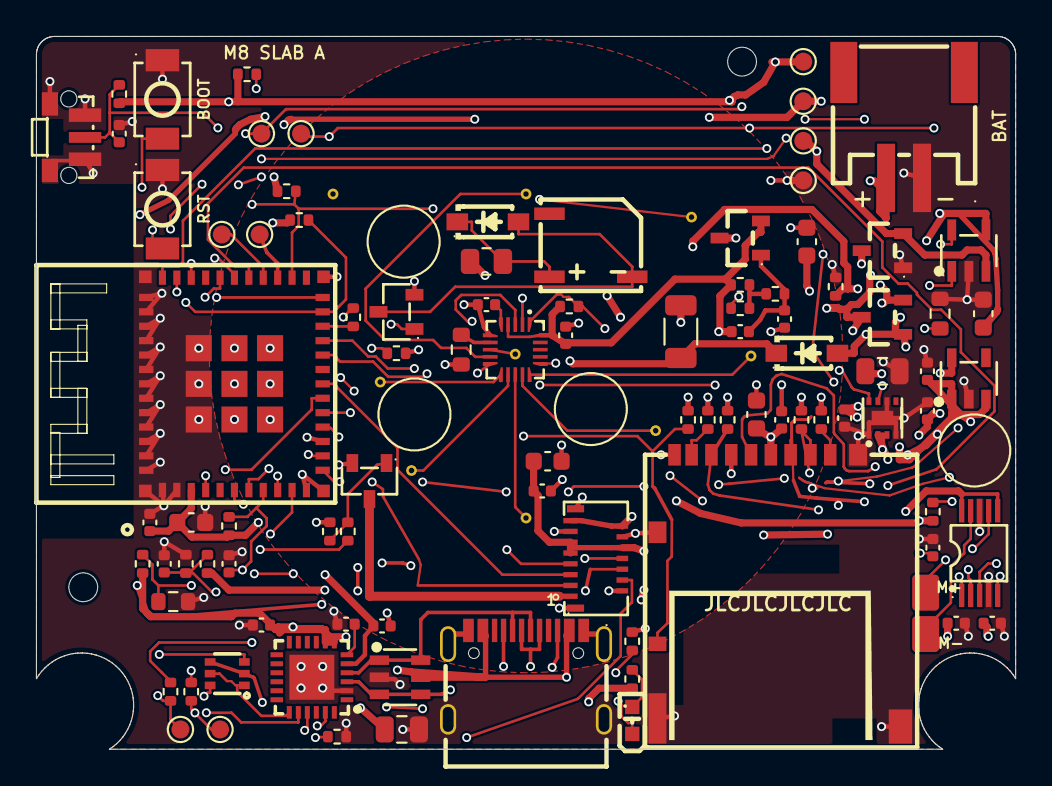
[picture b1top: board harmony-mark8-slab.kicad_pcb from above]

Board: 4 copper layers, 54.4 x 39.6 mm, 103 parts (0 on the bottom side), 70 nets.

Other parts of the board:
H1, H2: NPTH 1.6 locating; LocatingHole_NPTH_1.6
PP1, PP2, PP3, PP4: Press pad 4.0; PressPad_4.0

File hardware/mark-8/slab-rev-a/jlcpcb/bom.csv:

Comment,Designator,Footprint,LCSC Part #
MLT-5020,BZ1,Buzzer_MLT-5020,C94598
10uF,C1,C_0805_2012Metric,C15850
1uF,"C4,C10,C12,C15,C17,C18",C_0402_1005Metric,C52923
4.7uF,C11,C_0402_1005Metric,C23733
100nF,"C2,C3,C6,C13,C14,C16,C20,C22,C23,C24,C25,C26",C_0402_1005Metric,C1525
10uF,"C8,C19,C21",C_0603_1608Metric,C19702
22uF,C5,C_0603_1608Metric,C59461
4.7uF,C7,C_0603_1608Metric,C19666
22uF,C9,C_0805_2012Metric,C45783
B5819W SL,"D1,D2",SOD-123_B5819W,C8598
TYPE-C-31-M-12,J1,USB-C_HRO_TYPE-C-31-M-12,C165948
FH35C-15S-0.3SHW(50),J2,FH35C-15S-0.3SHW,C2889267
DM3AT-SF-PEJM5,J3,DM3AT-SF-PEJM5,C114218
S2B-PH-SM4-TB,J4,JST_PH_S2B-PH-SM4-TB,C54582899
Red,LED1,LED_0603_EasyEDA,C2286
UMH3N,Q1,SOT-363,C62892
AO3401A,"Q2,Q3,Q4",SOT-23_AO3401A,C15127
AO3400A,"Q5,Q6",SOT-23_AO3400A,C20917
5.1k,"R1,R2",R_0402_1005Metric,C25905
75k,"R10,R30",R_0603_1608Metric,C23242
10k,"R5,R6,R9,R11,R12,R21,R22,R23,R24",R_0402_1005Metric,C25744
2.2k,R13,R_0402_1005Metric,C25879
1k,"R3,R4,R8,R14",R_0402_1005Metric,C11702
100R,"R15,R19",R_0402_1005Metric,C25076
100k,"R16,R20,R26,R29",R_0402_1005Metric,C25741
10R,R17,R_1206_3216Metric,C17903
33R,R18,R_0805_2012Metric,C17634
1M,"R25,R27,R28",R_0402_1005Metric,C26083
4.7k,"R31,R32,R34",R_0402_1005Metric,C25900
2.7k,R7,R_0603_1608Metric,C13167
SIDE,SW1,SW_SKRTLAE010,C110293
BOOT/RESET,"SW2,SW3",SW_TS-1088,C720477
ESP32-PICO-MINI-02-N8R2,U1,ESP32-PICO-MINI-02,C2980306
CH9102F,U2,QFN-24_4x4_P0.5_EP2.5,C2858418
MCP73831T-2ACI/OT,U3,SOT-23-5_MCP73831,C424093
RT9080-33GJ5,U4,TSOT-23-5_RT9080,C841192
MAX17048G+T10,U5,TDFN-8_2x2_P0.5_EP,C2682616
MPR121QR2,U6,QFN-20_3x3_P0.4,C91322
DRV2605LDGSR,U7,VSSOP-10_DRV2605L,C527464
USBLC6-2SC6,U8,SOT-23-6,C7519

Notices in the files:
hardware/revisions/harmony-r3/tangara-faceplate/tangara-faceplate.kicad_sch:
SPDX-License-Identifier: CERN-OHL-S-2.0
parts and their libraries:
Copyright 2021 Accelerated Designs. All rights reserved.
